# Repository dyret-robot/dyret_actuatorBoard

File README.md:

# `dyret_actuatorBoard`

This repository contains the code and PCB design of the `dyret_actuatorBoard`.

## Documentation
For further documentation check out the
[wiki](https://github.com/dyret-robot/dyret_documentation/wiki).

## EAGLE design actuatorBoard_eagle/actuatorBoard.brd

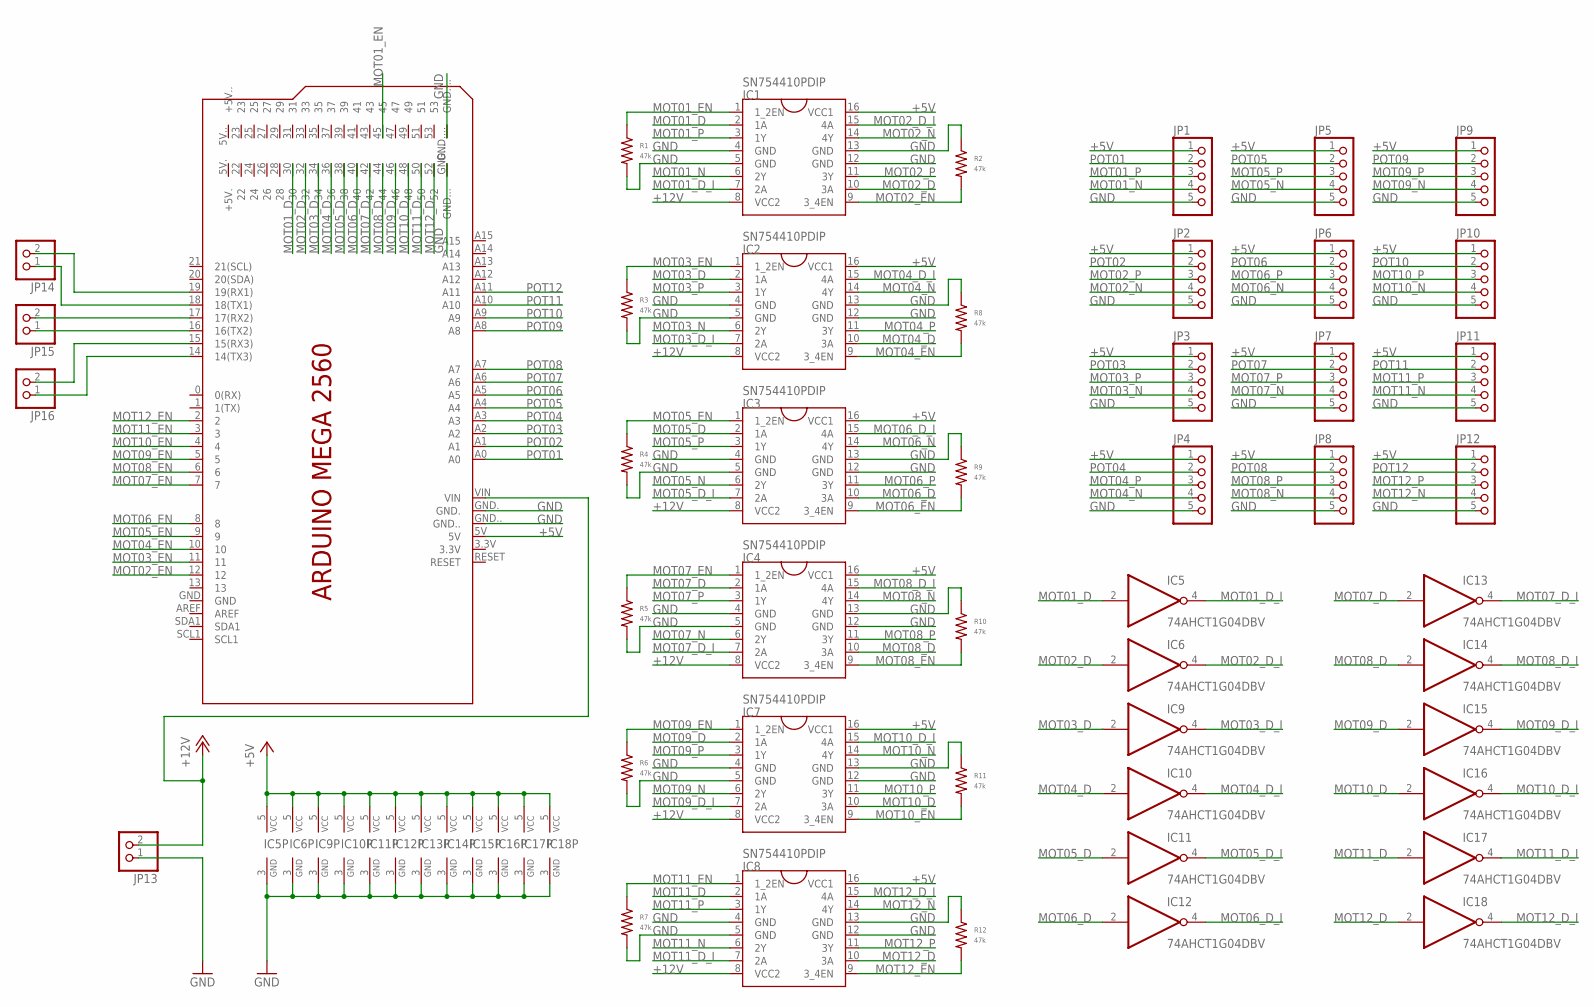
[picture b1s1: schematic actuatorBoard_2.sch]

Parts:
IC1, IC2, IC3, IC4, IC7, IC8: SN754410PDIP; DIL16
IC5, IC6, IC9, IC10, IC11, IC12, IC13, IC14, IC15, IC16, IC17, IC18: 74AHCT1G04DBV; SOT23-5
JP1, JP2, JP3, JP4, JP5, JP6, JP7, JP8, JP9, JP10, JP11, JP12: PINHD-1X5; 1X05
JP13, JP14, JP15, JP16: PINHD-1X2; 1X02
PCB1: ARDUINO_MEGA2560
R1, R2, R3, R4, R5, R6, R7, R8, R9, R10, R11, R12: 47k; R0603

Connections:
+5V: IC1.16 (VCC1), IC2.16 (VCC1), IC3.16 (VCC1), IC4.16 (VCC1), IC5.5 (VCC), IC6.5 (VCC), IC7.16 (VCC1), IC8.16 (VCC1), IC9.5 (VCC), IC10.5 (VCC), IC11.5 (VCC), IC12.5 (VCC), IC13.5 (VCC), IC14.5 (VCC), IC15.5 (VCC), IC16.5 (VCC), IC17.5 (VCC), IC18.5 (VCC), JP1.1, JP2.1, JP3.1, JP4.1, JP5.1, JP6.1, JP7.1, JP8.1, JP9.1, JP10.1, JP11.1, JP12.1, PCB1.5V
+12V: IC1.8 (VCC2), IC2.8 (VCC2), IC3.8 (VCC2), IC4.8 (VCC2), IC7.8 (VCC2), IC8.8 (VCC2), JP13.2, PCB1.VIN
GND: IC1.4 (GND), IC1.5 (GND), IC1.12 (GND), IC1.13 (GND), IC2.4 (GND), IC2.5 (GND), IC2.12 (GND), IC2.13 (GND), IC3.4 (GND), IC3.5 (GND), IC3.12 (GND), IC3.13 (GND), IC4.4 (GND), IC4.5 (GND), IC4.12 (GND), IC4.13 (GND), IC5.3 (GND), IC6.3 (GND), IC7.4 (GND), IC7.5 (GND), IC7.12 (GND), IC7.13 (GND), IC8.4 (GND), IC8.5 (GND), IC8.12 (GND), IC8.13 (GND), IC9.3 (GND), IC10.3 (GND), IC11.3 (GND), IC12.3 (GND), IC13.3 (GND), IC14.3 (GND), IC15.3 (GND), IC16.3 (GND), IC17.3 (GND), IC18.3 (GND), JP1.5, JP2.5, JP3.5, JP4.5, JP5.5, JP6.5, JP7.5, JP8.5, JP9.5, JP10.5, JP11.5, JP12.5, JP13.1, PCB1.GND., PCB1.GND.., PCB1.GND..., PCB1.GND...., R1.P$2, R2.P$1, R3.P$2, R4.P$2, R5.P$2, R6.P$2, R7.P$2, R8.P$1, R9.P$1, R10.P$1, R11.P$1, R12.P$1
MOT01_D: IC1.2 (1A), IC5.2 (I), PCB1.30
MOT01_D_I: IC1.7 (2A), IC5.4 (O)
MOT01_EN: IC1.1 (1_2EN), PCB1.45, R1.P$1
MOT01_N: IC1.6 (2Y), JP1.4
MOT01_P: IC1.3 (1Y), JP1.3
MOT02_D: IC1.10 (3A), IC6.2 (I), PCB1.32
MOT02_D_I: IC1.15 (4A), IC6.4 (O)
MOT02_EN: IC1.9 (3_4EN), PCB1.12, R2.P$2
MOT02_N: IC1.14 (4Y), JP2.4
MOT02_P: IC1.11 (3Y), JP2.3
MOT03_D: IC2.2 (1A), IC9.2 (I), PCB1.34
MOT03_D_I: IC2.7 (2A), IC9.4 (O)
MOT03_EN: IC2.1 (1_2EN), PCB1.11, R3.P$1
MOT03_N: IC2.6 (2Y), JP3.4
MOT03_P: IC2.3 (1Y), JP3.3
MOT04_D: IC2.10 (3A), IC10.2 (I), PCB1.36
MOT04_D_I: IC2.15 (4A), IC10.4 (O)
MOT04_EN: IC2.9 (3_4EN), PCB1.10, R8.P$2
MOT04_N: IC2.14 (4Y), JP4.4
MOT04_P: IC2.11 (3Y), JP4.3
MOT05_D: IC3.2 (1A), IC11.2 (I), PCB1.38
MOT05_D_I: IC3.7 (2A), IC11.4 (O)
MOT05_EN: IC3.1 (1_2EN), PCB1.9, R4.P$1
MOT05_N: IC3.6 (2Y), JP5.4
MOT05_P: IC3.3 (1Y), JP5.3
MOT06_D: IC3.10 (3A), IC12.2 (I), PCB1.40
MOT06_D_I: IC3.15 (4A), IC12.4 (O)
MOT06_EN: IC3.9 (3_4EN), PCB1.8, R9.P$2
MOT06_N: IC3.14 (4Y), JP6.4
MOT06_P: IC3.11 (3Y), JP6.3
MOT07_D: IC4.2 (1A), IC13.2 (I), PCB1.42
MOT07_D_I: IC4.7 (2A), IC13.4 (O)
MOT07_EN: IC4.1 (1_2EN), PCB1.7, R5.P$1
MOT07_N: IC4.6 (2Y), JP7.4
MOT07_P: IC4.3 (1Y), JP7.3
MOT08_D: IC4.10 (3A), IC14.2 (I), PCB1.44
MOT08_D_I: IC4.15 (4A), IC14.4 (O)
MOT08_EN: IC4.9 (3_4EN), PCB1.6, R10.P$2
MOT08_N: IC4.14 (4Y), JP8.4
MOT08_P: IC4.11 (3Y), JP8.3
MOT09_D: IC7.2 (1A), IC15.2 (I), PCB1.46
MOT09_D_I: IC7.7 (2A), IC15.4 (O)
MOT09_EN: IC7.1 (1_2EN), PCB1.5, R6.P$1
MOT09_N: IC7.6 (2Y), JP9.4
MOT09_P: IC7.3 (1Y), JP9.3
MOT10_D: IC7.10 (3A), IC16.2 (I), PCB1.48
MOT10_D_I: IC7.15 (4A), IC16.4 (O)
MOT10_EN: IC7.9 (3_4EN), PCB1.4, R11.P$2
MOT10_N: IC7.14 (4Y), JP10.4
MOT10_P: IC7.11 (3Y), JP10.3
MOT11_D: IC8.2 (1A), IC17.2 (I), PCB1.50
MOT11_D_I: IC8.7 (2A), IC17.4 (O)
MOT11_EN: IC8.1 (1_2EN), PCB1.3, R7.P$1
MOT11_N: IC8.6 (2Y), JP11.4
MOT11_P: IC8.3 (1Y), JP11.3
MOT12_D: IC8.10 (3A), IC18.2 (I), PCB1.52
MOT12_D_I: IC8.15 (4A), IC18.4 (O)
MOT12_EN: IC8.9 (3_4EN), PCB1.2, R12.P$2
MOT12_N: IC8.14 (4Y), JP12.4
MOT12_P: IC8.11 (3Y), JP12.3
unnamed: JP15.2, PCB1.17 (17(RX2))
unnamed: JP15.1, PCB1.16 (16(TX2))
unnamed: JP14.1, PCB1.18 (18(TX1))
unnamed: JP14.2, PCB1.19 (19(RX1))
unnamed: JP16.2, PCB1.15 (15(RX3))
unnamed: JP16.1, PCB1.14 (14(TX3))
POT01: JP1.2, PCB1.A0
POT02: JP2.2, PCB1.A1
POT03: JP3.2, PCB1.A2
POT04: JP4.2, PCB1.A3
POT05: JP5.2, PCB1.A4
POT06: JP6.2, PCB1.A5
POT07: JP7.2, PCB1.A6
POT08: JP8.2, PCB1.A7
POT09: JP9.2, PCB1.A8
POT10: JP10.2, PCB1.A9
POT11: JP11.2, PCB1.A10
POT12: JP12.2, PCB1.A11

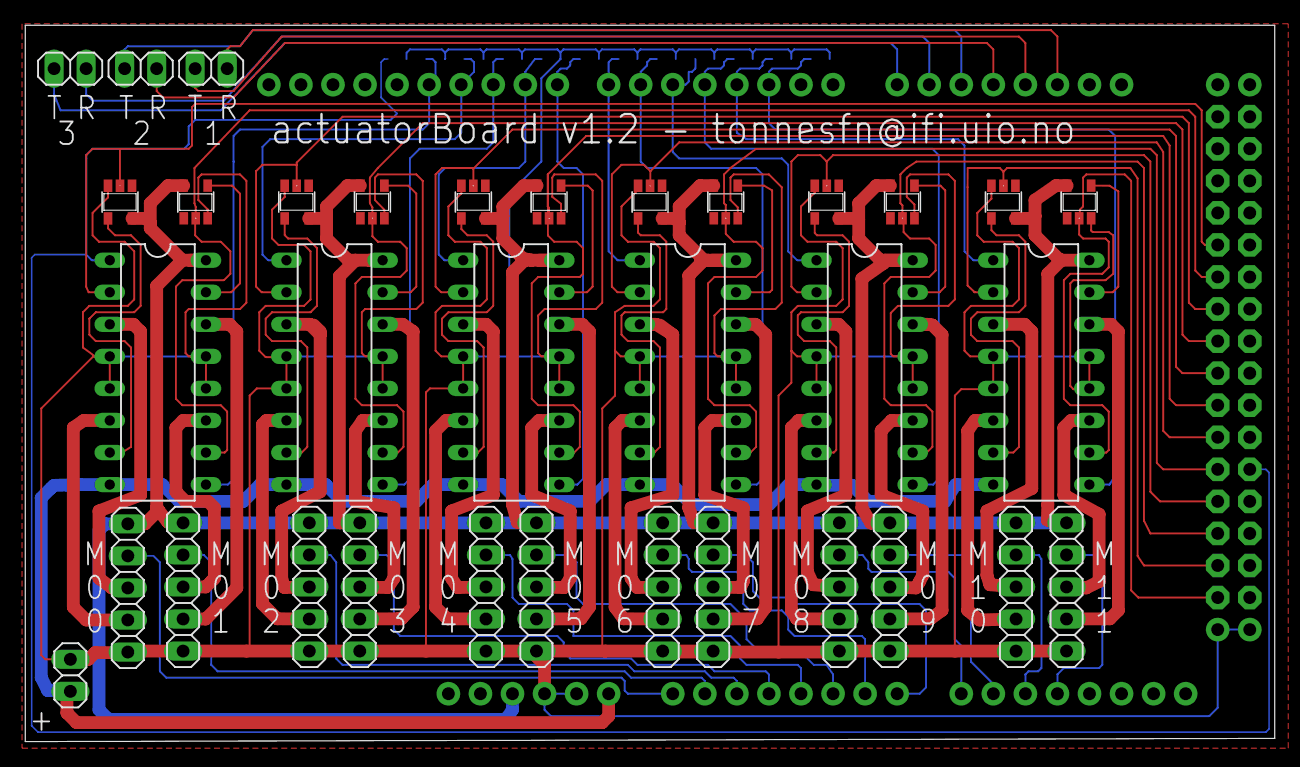
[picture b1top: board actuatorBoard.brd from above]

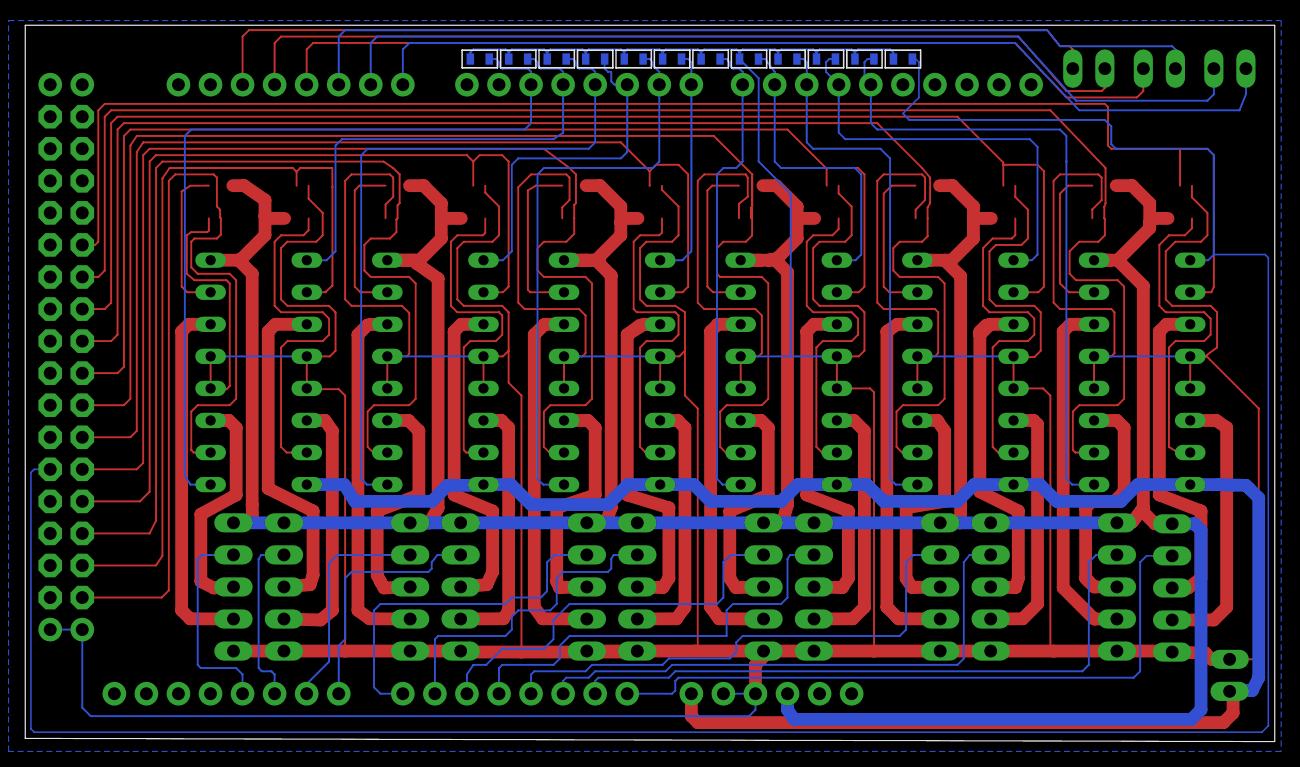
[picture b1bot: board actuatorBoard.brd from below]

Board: 2 copper layers, 99.0 x 56.8 mm, 47 parts (12 on the bottom side), 81 nets.

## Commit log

2017-10-05 Added actuatorBoard_arduinoTester
2017-10-05 Added pin definitions
2017-10-05 Added safety feature when reaching position 0 during control
2017-10-05 Fixed error in position calculation
2017-10-05 Slightly improved reset of actuators to return to sensed 0 pos
2017-10-09 Added debugging of communications
2017-10-10 Added interval execution of message sending and motor control
2017-10-10 Fixed formating and message setup functions
2017-10-10 Removed separate leg zeroing function
2017-10-13 Added two special cases for controlling all actuators
2017-10-30 Added support for 15V operation of board
2017-10-30 Added limits to lengths
2017-12-07 Added blocking while zeroing legs
2018-06-01 Removed debug message and added new topic names and message types
2018-06-01 Iteration on actuatorBoard
2018-06-18 Prepare for publication on github.com
2019-06-11 Added error detection for stuck motors
2019-06-11 Added reset of error on new command

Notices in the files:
README.md:
License: GPL v3
License: CC BY-SA 4.0
